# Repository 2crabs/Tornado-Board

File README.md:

<p align="center">
    <picture>
      <source media="(prefers-color-scheme: dark)" srcset="Images/logo-darkTheme.png">
      <source media="(prefers-color-scheme: light)" srcset="Images/logo-lightTheme.png">
      
    </picture>
</p>

---

Tornado is a fully open-source IMU board built for FRC

## Block Diagram

## Resources
* [Schematic](Images/Schematic.pdf)

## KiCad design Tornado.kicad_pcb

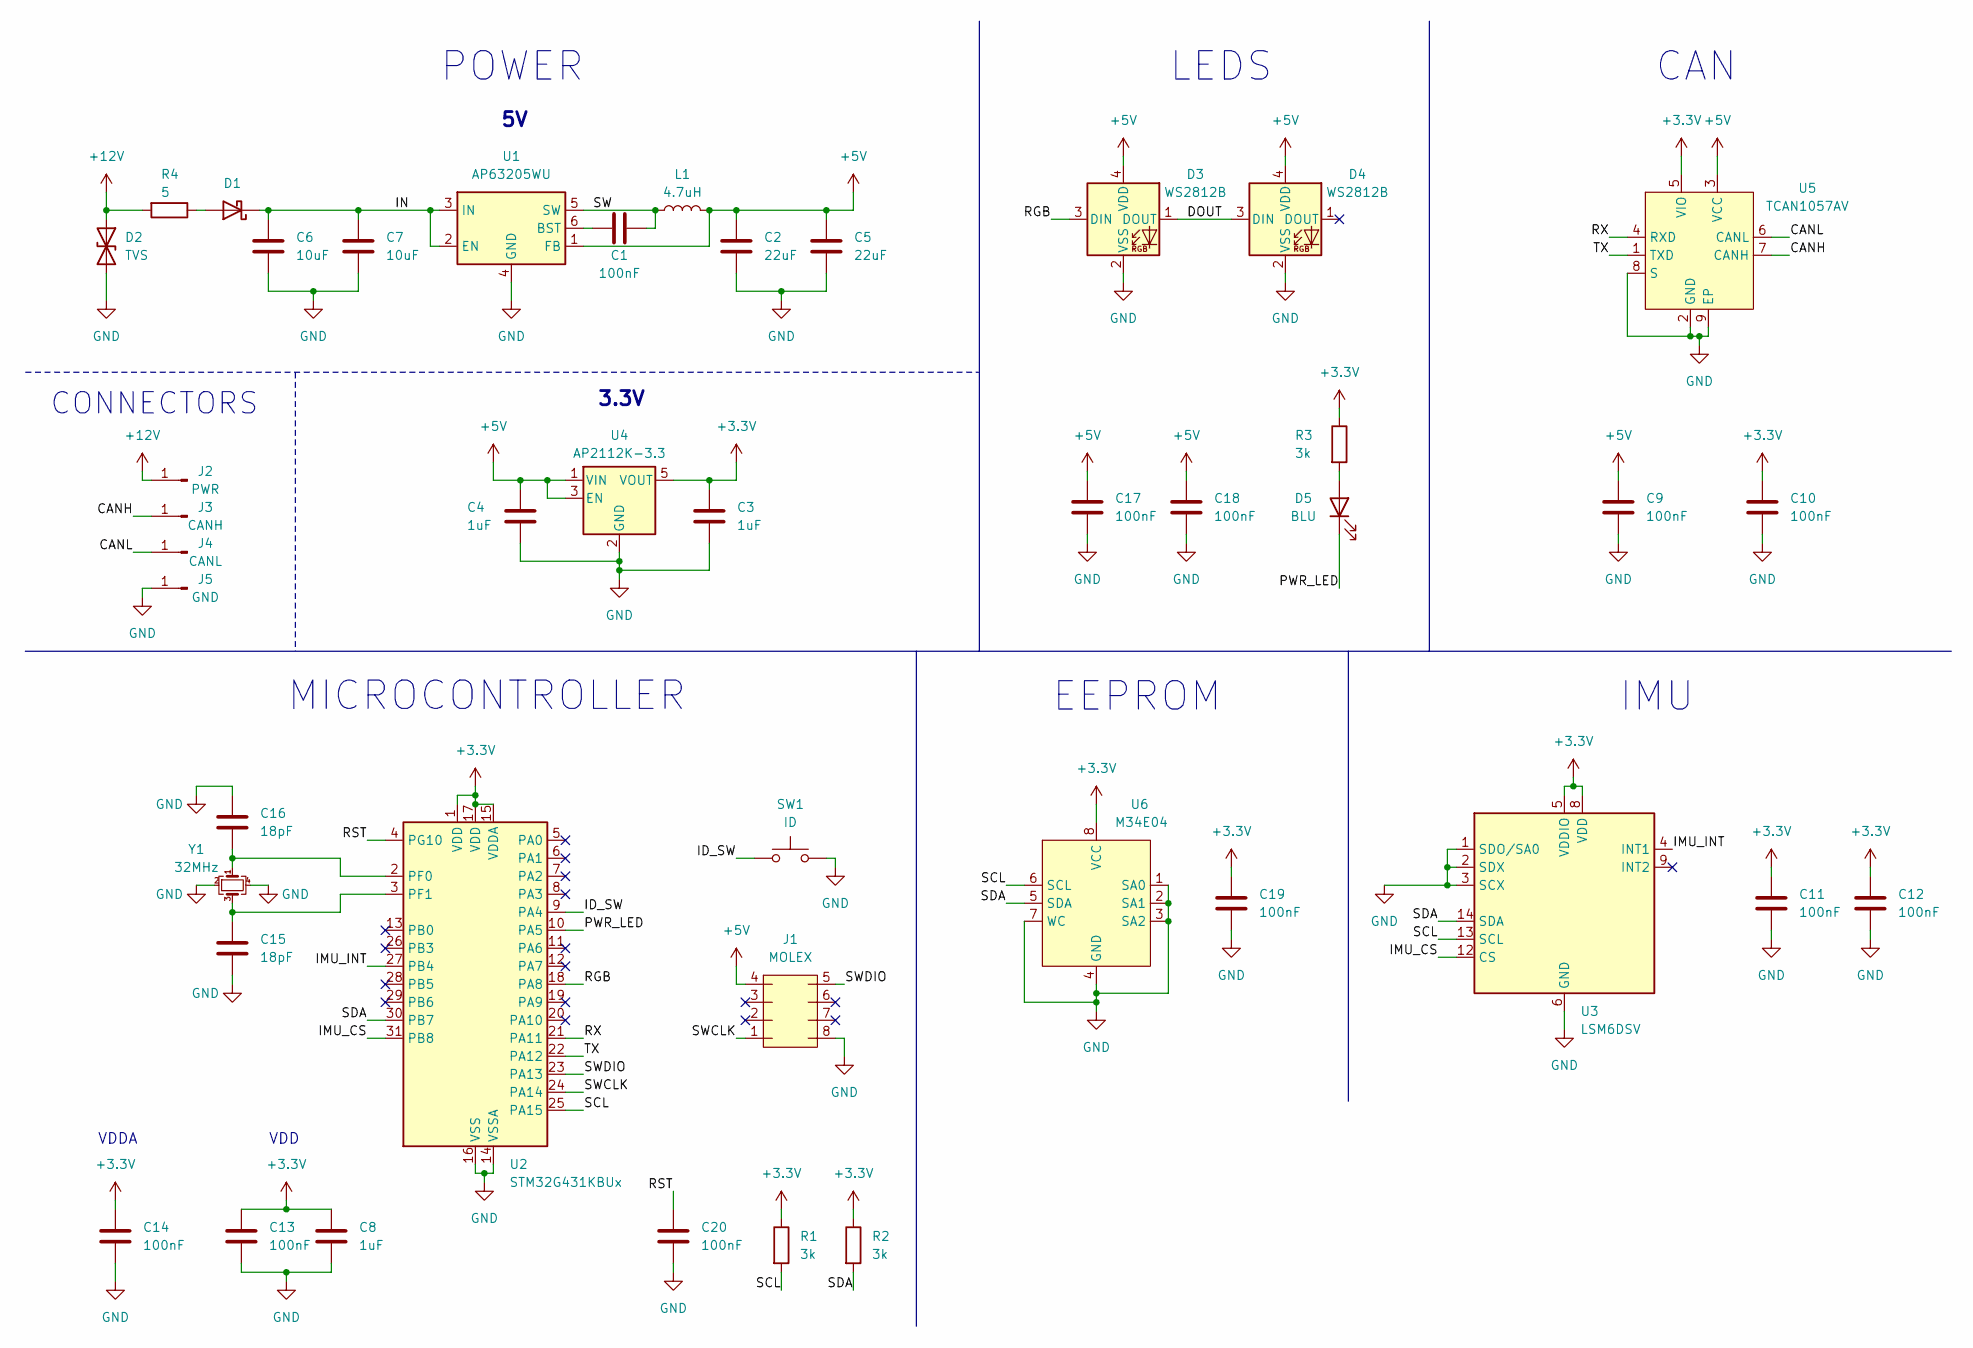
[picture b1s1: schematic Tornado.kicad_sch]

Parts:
C1, C9, C10, C11, C12, C13, C14, C17, C18, C19, C20: 100nF; C_0402_1005Metric
C2, C5: 22uF; C_0805_2012Metric
C3, C4, C8: 1uF; C_0603_1608Metric
C6, C7: 10uF; C_0805_2012Metric
C15, C16: 18pF; C_0603_1608Metric
D1: D_Schottky; D_SOD-523
D2: TVS; D_SOD-323
D3, D4: WS2812B; WS2812B-2020
D5: BLU; LED_0603_1608Metric
J1: MOLEX; 5050040812-MOLEX
J2: PWR; Wire_Hole
J3: CANH; Wire_Hole
J4: CANL; Wire_Hole
J5: GND; Wire_Hole
L1: 4.7uH; L_1008_2520Metric
R1, R2, R3: 3k; R_0603_1608Metric
R4: 5; R_0603_1608Metric
SW1: ID; TC029
U1: AP63205WU; TSOT-23-6
U2: STM32G431KBUx; QFN-32-1EP_5x5mm_P0.5mm_EP3.45x3.45mm
U3: LSM6DSV; LGA-14_3x2.5mm_P0.5mm_LayoutBorder3x4y
U4: AP2112K-3.3; SOT-23-5
U5: TCAN1057AV
U6: M34E04; 8-UFDFPN
Y1: 32MHz; Crystal_SMD_3225-4Pin_3.2x2.5mm

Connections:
+3.3V: C3.1, C8.1, C10.1, C11.1, C12.1, C13.1, C14.1, C19.1, R1.1, R2.1, R3.1, U2.1 (VDD), U2.15 (VDDA), U2.17 (VDD), U3.5 (VDDIO), U3.8 (VDD), U4.5 (VOUT), U5.5 (VIO), U6.8 (VCC)
+5V: C2.1, C4.1, C5.1, C9.1, C17.1, C18.1, D3.4 (VDD), D4.4 (VDD), J1.4, L1.2, U1.1 (FB), U4.1 (VIN), U4.3 (EN), U5.3 (VCC)
+12V: D2.1 (A1), J2.1, R4.2
/CANH: J3.1, U5.7 (CANH); also elsewhere on the board
/CANL: J4.1, U5.6 (CANL); also elsewhere on the board
/DOUT: D3.1 (DOUT), D4.3 (DIN)
/ID_SW: SW1.1, U2.9 (PA4)
/IMU_CS: U2.31 (PB8), U3.12 (CS)
/IMU_INT: U2.27 (PB4), U3.4 (INT1)
/IN: C6.2, C7.1, D1.1 (K), U1.2 (EN), U1.3 (IN)
/PWR_LED: D5.1 (K), U2.10 (PA5)
/RGB: D3.3 (DIN), U2.18 (PA8)
/RST: C20.1, U2.4 (PG10)
/RX: U2.21 (PA11), U5.4 (RXD)
/SCL: R1.2, U2.25 (PA15), U3.13 (SCL), U6.6 (SCL)
/SDA: R2.2, U2.30 (PB7), U3.14 (SDA), U6.5 (SDA)
/SW: C1.1, L1.1, U1.5 (SW)
/SWCLK: J1.1, U2.24 (PA14)
/SWDIO: J1.5, U2.23 (PA13)
/TX: U2.22 (PA12), U5.1 (TXD)
GND: C2.2, C3.2, C4.2, C5.2, C6.1, C7.2, C8.2, C9.2, C10.2, C11.2, C12.2, C13.2, C14.2, C15.2, C16.1, C17.2, C18.2, C19.2, C20.2, D2.2 (A2), D3.2 (VSS), D4.2 (VSS), J1.8, J5.1, SW1.2, U1.4 (GND), U2.14 (VSSA), U2.16 (VSS), U2.32 (VSS), U2.33 (VSS), U3.1 (SDO/SA0), U3.2 (SDX), U3.3 (SCX), U3.6 (GND), U3.7 (GND), U4.2 (GND), U5.2 (GND), U5.8 (S), U5.9 (EP), U6.1 (SA0), U6.2 (SA1), U6.3 (SA2), U6.4 (GND), U6.7 (WC), Y1.2, Y1.4
unnamed: D1.2 (A), R4.1
unnamed: D5.2 (A), R3.2
unnamed: C1.2, U1.6 (BST)
unnamed: C16.2, U2.2 (PF0), Y1.1
unnamed: C15.1, U2.3 (PF1), Y1.3

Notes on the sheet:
CONNECTORS
IMU
VDD
LEDS
MICROCONTROLLER
3.3V
POWER
EEPROM
CAN
VDDA

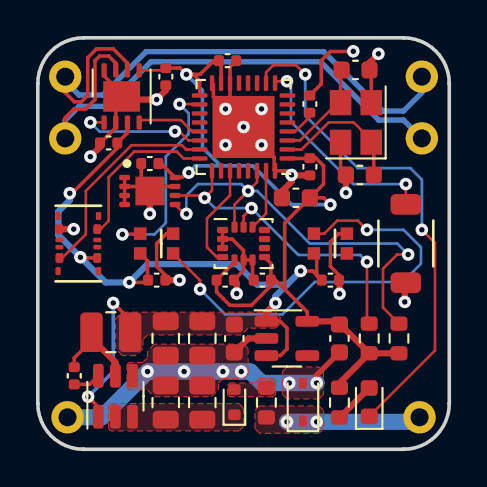
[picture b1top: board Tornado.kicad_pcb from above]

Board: 4 copper layers, 22.9 x 22.9 mm, 45 parts (0 on the bottom side), 26 nets.

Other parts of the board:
J3#2: CANH; Wire_Hole
J4#2: CANL; Wire_Hole

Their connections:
/CANH: J3#2.1; also elsewhere on the board
/CANL: J4#2.1; also elsewhere on the board

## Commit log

2024-07-23 Added project files
2024-08-27 Added graphics
2024-09-29 Hid unused text
2024-09-29 Fixed Copper Pour
2024-09-29 Fixed silkscreen
2024-10-03 Changed ESD diode
2024-10-04 Replaced pads with holes
2024-11-05 Added Silkscreen
2024-11-05 Added Ferrite Bead
2025-02-16 Added License
2025-02-16 Removed Unused Library
2025-02-16 Updated RGB Symbol
2025-02-16 Added Resource files
2025-02-17 Basic readme
2025-02-19 Improved Readme
2025-02-27 Added new Image to readme
2025-02-28 Added block diagram
2025-03-01 Added resistor to filter
